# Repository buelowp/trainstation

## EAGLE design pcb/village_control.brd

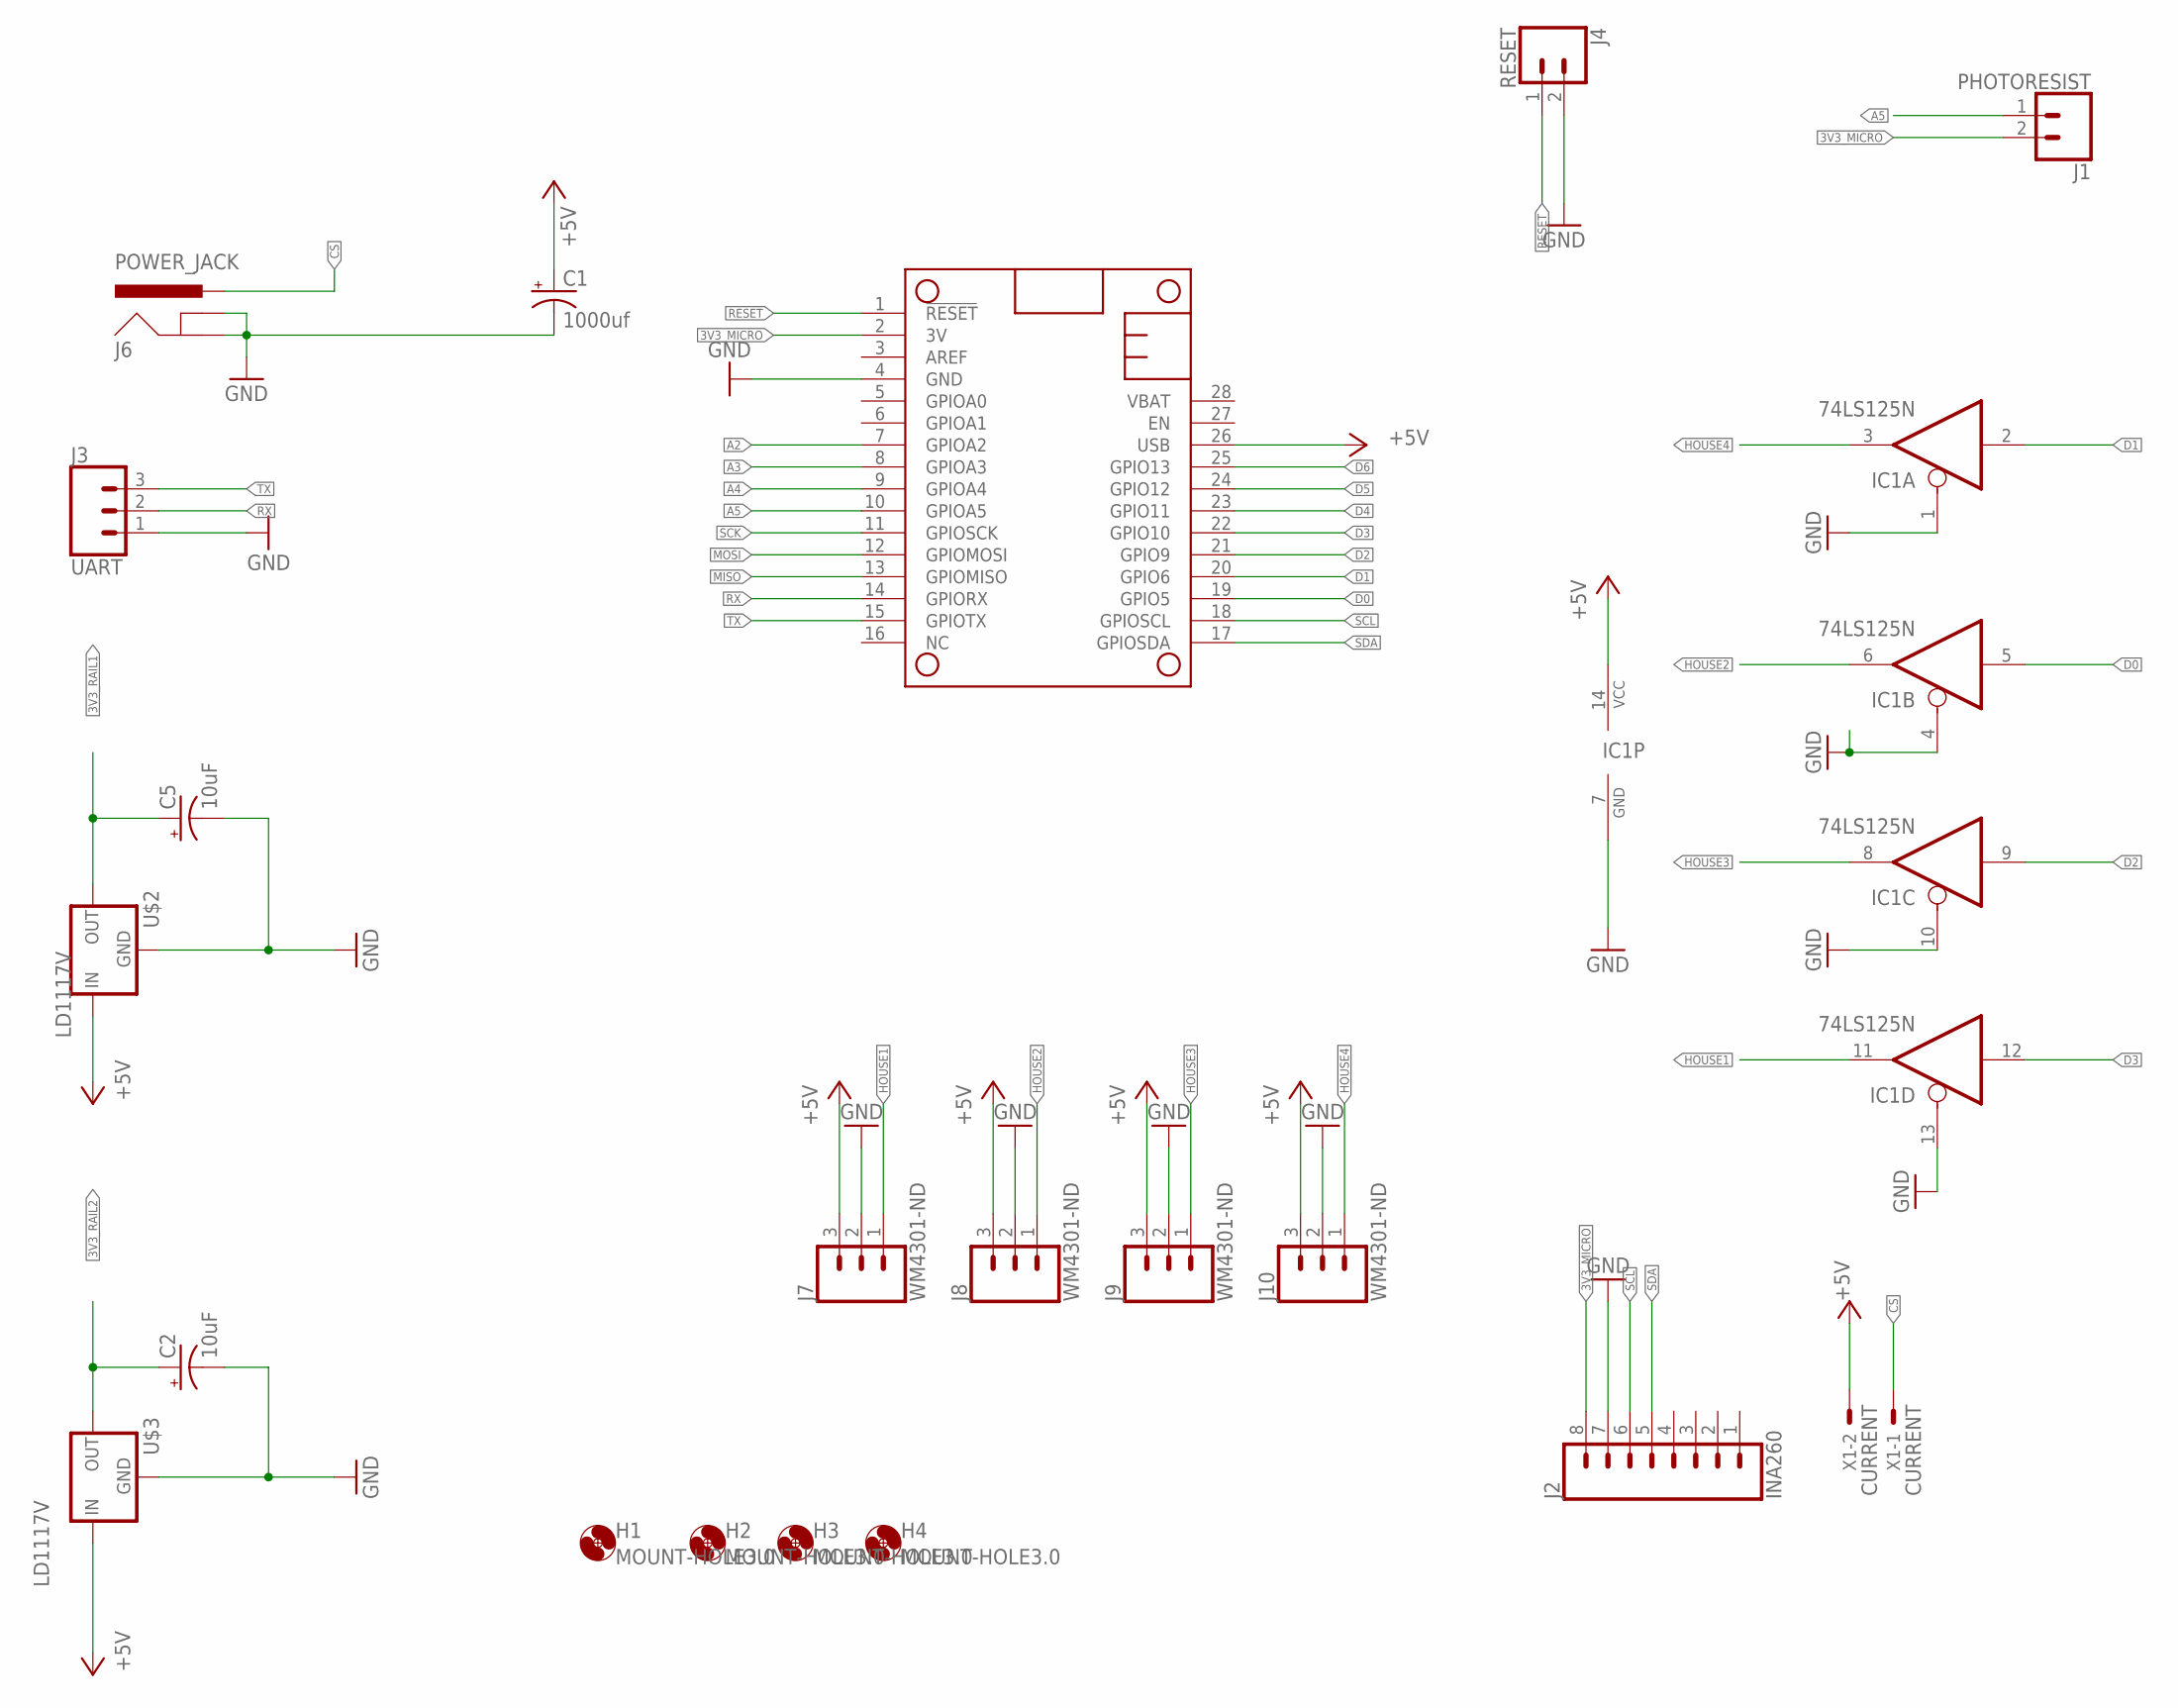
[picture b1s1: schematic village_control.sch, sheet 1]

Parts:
C1: 1000uf; CPOL-RADIAL-5MM-10MM
C2, C5: 10uF; CPOL-RADIAL-2.5MM-5MM-KIT
H1, H2, H3, H4: MOUNT-HOLE3.0; 3,0
IC1: 74LS125N; DIL14
J1: PHOTORESIST; 1X02
J2: INA260; 1X08
J3: UART; 1X03
J4: RESET; 1X02
J6: POWER_JACK; POWER_JACK_PTH
J7, J8, J9, J10: WM4301-ND; 1X03
MS2: FEATHERWING_NODIM; FEATHERWING_DIM
U$2, U$3: LD1117V; 78XXL
X1: CURRENT; KK-156-2

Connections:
3V3_MICRO: J1.2, J2.8, MS2.2 (3V)
3V3_RAIL1: C5.1 (+), U$2.GND (OUT); also elsewhere on the board
3V3_RAIL2: C2.1 (+), U$3.GND (OUT); also elsewhere on the board
+5V: C1.+, IC1.14 (VCC), J7.3, J8.3, J9.3, J10.3, MS2.26 (USB), U$2.OUT (IN), U$3.OUT (IN), X1.2; also elsewhere on the board
A2: MS2.7 (GPIOA2); also elsewhere on the board
A3: MS2.8 (GPIOA3); also elsewhere on the board
A4: MS2.9 (GPIOA4); also elsewhere on the board
A5: J1.1, MS2.10 (GPIOA5)
CS: J6.PWR, X1.1
D0: IC1.5 (I), MS2.19 (GPIO5)
D1: IC1.2 (I), MS2.20 (GPIO6)
D2: IC1.9 (I), MS2.21 (GPIO9)
D3: IC1.12 (I), MS2.22 (GPIO10)
D4: MS2.23 (GPIO11); also elsewhere on the board
D5: MS2.24 (GPIO12); also elsewhere on the board
D6: MS2.25 (GPIO13); also elsewhere on the board
GND: C1.-, C2.2 (-), C5.2 (-), IC1.1 (OE), IC1.4 (OE), IC1.7 (GND), IC1.10 (OE), IC1.13 (OE), J2.7, J3.1, J4.2, J6.GND, J6.GNDBREAK, J7.2, J8.2, J9.2, J10.2, MS2.4 (GND), U$2.IN (GND), U$3.IN (GND); also elsewhere on the board
HOUSE1: IC1.11 (O), J7.1
HOUSE2: IC1.6 (O), J8.1
HOUSE3: IC1.8 (O), J9.1
HOUSE4: IC1.3 (O), J10.1
MISO: MS2.13 (GPIOMISO); also elsewhere on the board
MOSI: MS2.12 (GPIOMOSI); also elsewhere on the board
RESET: J4.1, MS2.1 (!RESET)
RX: J3.2, MS2.14 (GPIORX)
SCK: MS2.11 (GPIOSCK); also elsewhere on the board
SCL: J2.6, MS2.18 (GPIOSCL)
SDA: J2.5, MS2.17 (GPIOSDA)
TX: J3.3, MS2.15 (GPIOTX)

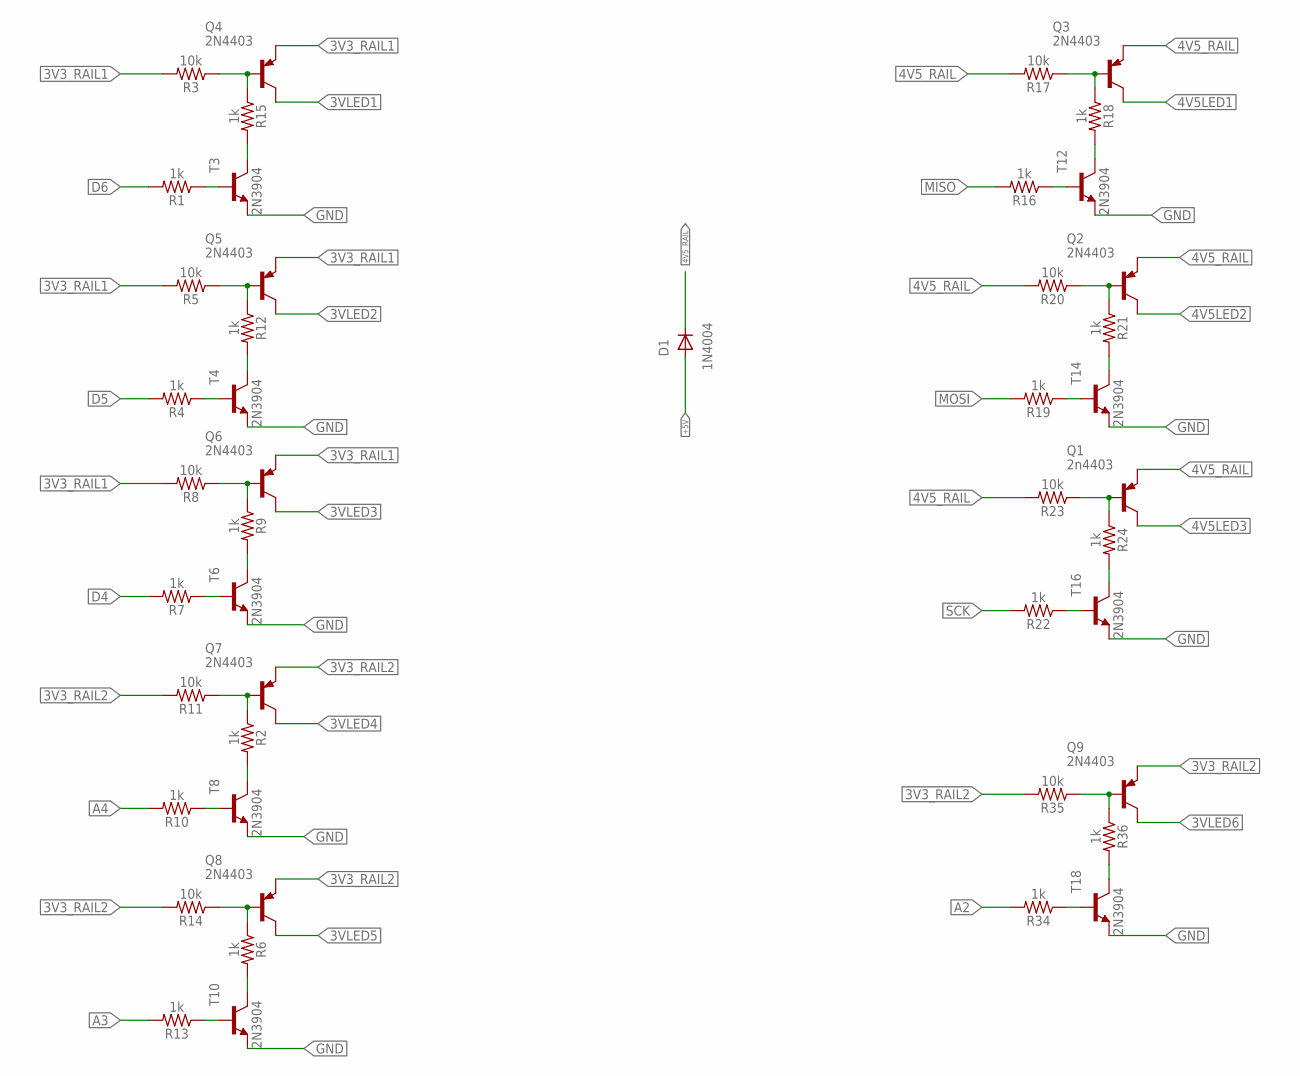
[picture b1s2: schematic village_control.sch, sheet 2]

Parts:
D1: 1N4004; DO41-10
Q1: 2n4403; TO92
Q2, Q3, Q4, Q5, Q6, Q7, Q8, Q9: 2N4403; TO92
R1, R2, R4, R6, R7, R9, R10, R12, R13, R15, R16, R18, R19, R21, R22, R24, R34, R36: 1k; AXIAL-0.3
R3, R5, R8, R11, R14, R17, R20, R23, R35: 10k; AXIAL-0.3
T3, T4, T6, T8, T10, T12, T14, T16, T18: 2N3904; TO92

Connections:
3V3_RAIL1: Q4.3 (E), Q5.3 (E), Q6.3 (E), R3.P$2 (2), R5.P$2 (2), R8.P$2 (2); also elsewhere on the board
3V3_RAIL2: Q7.3 (E), Q8.3 (E), Q9.3 (E), R11.P$2 (2), R14.P$2 (2), R35.P$2 (2); also elsewhere on the board
3VLED1: Q4.1 (C); also elsewhere on the board
3VLED2: Q5.1 (C); also elsewhere on the board
3VLED3: Q6.1 (C); also elsewhere on the board
3VLED4: Q7.1 (C); also elsewhere on the board
3VLED5: Q8.1 (C); also elsewhere on the board
3VLED6: Q9.1 (C); also elsewhere on the board
4V5LED1: Q3.1 (C); also elsewhere on the board
4V5LED2: Q2.1 (C); also elsewhere on the board
4V5LED3: Q1.1 (C); also elsewhere on the board
4V5_RAIL: D1.C, Q1.3 (E), Q2.3 (E), Q3.3 (E), R17.P$2 (2), R20.P$2 (2), R23.P$2 (2)
+5V: D1.A; also elsewhere on the board
A2: R34.P$2 (2); also elsewhere on the board
A3: R13.P$2 (2); also elsewhere on the board
A4: R10.P$2 (2); also elsewhere on the board
D4: R7.P$2 (2); also elsewhere on the board
D5: R4.P$2 (2); also elsewhere on the board
D6: R1.P$2 (2); also elsewhere on the board
GND: T3.3 (E), T4.3 (E), T6.3 (E), T8.3 (E), T10.3 (E), T12.3 (E), T14.3 (E), T16.3 (E), T18.3 (E); also elsewhere on the board
MISO: R16.P$2 (2); also elsewhere on the board
MOSI: R19.P$2 (2); also elsewhere on the board
unnamed: Q4.2 (B), R3.P$1 (1), R15.P$1 (1)
unnamed: R9.P$2 (2), T6.1 (C)
unnamed: R4.P$1 (1), T4.2 (B)
unnamed: R2.P$2 (2), T8.1 (C)
unnamed: R7.P$1 (1), T6.2 (B)
unnamed: R6.P$2 (2), T10.1 (C)
unnamed: Q6.2 (B), R8.P$1 (1), R9.P$1 (1)
unnamed: R12.P$2 (2), T4.1 (C)
unnamed: R10.P$1 (1), T8.2 (B)
unnamed: R1.P$1 (1), T3.2 (B)
unnamed: Q7.2 (B), R2.P$1 (1), R11.P$1 (1)
unnamed: R15.P$2 (2), T3.1 (C)
unnamed: R13.P$1 (1), T10.2 (B)
unnamed: Q8.2 (B), R6.P$1 (1), R14.P$1 (1)
unnamed: R36.P$2 (2), T18.1 (C)
unnamed: R16.P$1 (1), T12.2 (B)
unnamed: Q5.2 (B), R5.P$1 (1), R12.P$1 (1)
unnamed: Q3.2 (B), R17.P$1 (1), R18.P$1 (1)
unnamed: R24.P$2 (2), T16.1 (C)
unnamed: R19.P$1 (1), T14.2 (B)
unnamed: Q2.2 (B), R20.P$1 (1), R21.P$1 (1)
unnamed: R21.P$2 (2), T14.1 (C)
unnamed: R22.P$1 (1), T16.2 (B)
unnamed: Q1.2 (B), R23.P$1 (1), R24.P$1 (1)
unnamed: R18.P$2 (2), T12.1 (C)
unnamed: R34.P$1 (1), T18.2 (B)
unnamed: Q9.2 (B), R35.P$1 (1), R36.P$1 (1)
SCK: R22.P$2 (2); also elsewhere on the board

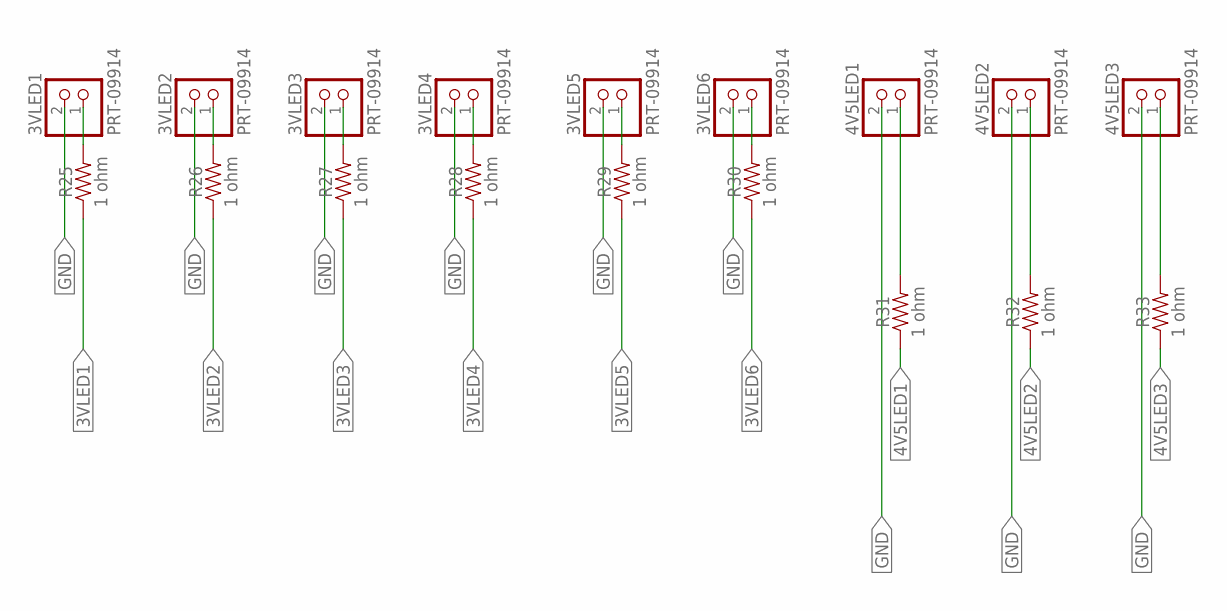
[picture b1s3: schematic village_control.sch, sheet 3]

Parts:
3VLED1, 3VLED2, 3VLED3, 3VLED4, 3VLED5, 3VLED6, 4V5LED1, 4V5LED2, 4V5LED3: PRT-09914; JST-PH-2-THM
R25, R26, R27, R28, R29, R30, R31, R32, R33: 1 ohm; AXIAL-0.3

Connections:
3VLED1: R25.P$1 (1); also elsewhere on the board
3VLED2: R26.P$1 (1); also elsewhere on the board
3VLED3: R27.P$1 (1); also elsewhere on the board
3VLED4: R28.P$1 (1); also elsewhere on the board
3VLED5: R29.P$1 (1); also elsewhere on the board
3VLED6: R30.P$1 (1); also elsewhere on the board
4V5LED1: R31.P$1 (1); also elsewhere on the board
4V5LED2: R32.P$1 (1); also elsewhere on the board
4V5LED3: R33.P$1 (1); also elsewhere on the board
GND: 3VLED1.2 (1), 3VLED2.2 (1), 3VLED3.2 (1), 3VLED4.2 (1), 3VLED5.2 (1), 3VLED6.2 (1), 4V5LED1.2 (1), 4V5LED2.2 (1), 4V5LED3.2 (1); also elsewhere on the board
unnamed: 3VLED1.1 (2), R25.P$2 (2)
unnamed: 4V5LED1.1 (2), R31.P$2 (2)
unnamed: 3VLED2.1 (2), R26.P$2 (2)
unnamed: 4V5LED2.1 (2), R32.P$2 (2)
unnamed: 3VLED3.1 (2), R27.P$2 (2)
unnamed: 4V5LED3.1 (2), R33.P$2 (2)
unnamed: 3VLED4.1 (2), R28.P$2 (2)
unnamed: 3VLED5.1 (2), R29.P$2 (2)
unnamed: 3VLED6.1 (2), R30.P$2 (2)

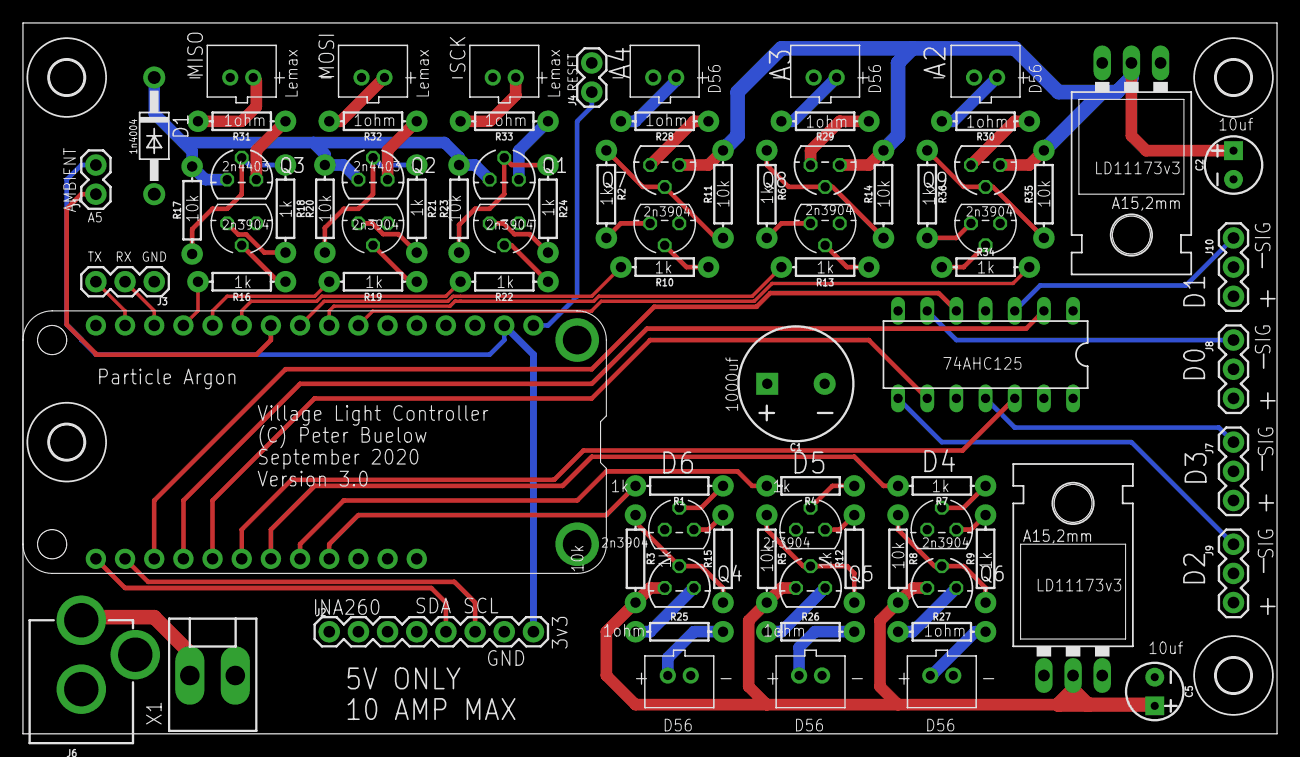
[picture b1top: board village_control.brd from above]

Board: 4 copper layers, 109.2 x 61.9 mm, 85 parts (0 on the bottom side), 75 nets.

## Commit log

2020-04-17 blink was running full bore, it never switched.
2020-09-03 Updating to Particle build system
2020-09-06 Continue to develop
    * Added some lights on and off logic, needs testing
2020-09-07 Checkpoint
    * Fixed it so the lights do what we need them to
    * Seperated the FastLED and Adafruit connections into classes to make it easier to manage the different parts
    * Added new gitignore
2020-09-07 Checkpoint
    * Added a block class to handle a collection of houses
    * Fixed up houses with logging and a few logical changes
    * Modified loop() to turn houses on and off randomly I believe, still testing
2020-09-08 New functionality
    * Added the ability to control the individual LED pins, which are street lamps mostly
    * Fixed a lot of bugs with the houses, and blocks of houses logic
    * Fixed a lot of logic related to turning on and off houses around sunrise and sunset
2020-09-08 Adding the controller PCB to the stored contents
2020-09-09 Fixing a bug
    * I switched the parameters for hasBeenTested() in turnOffRandomHouse() which caused some issues
    * Made the 1 minute HB print one hour just cause
2020-09-16 Lots of fixes.
    * Fixed bugs related to when lights turn on and off
    * Cleaned up logic issues
    * Made sure timeset only runs once
2020-09-18 Many fixes
    * Fixed an issue where the station didn't start correctly, so it wouldn't turn off
    * Fixed some indexing issues for the FastLED CRGB arrays
    * Many printing changes
    * Work towards fixing the number of lights that turn on/off in the random, still seems to have an issue
2020-10-10 Various fixes
2020-10-13 Migrating to new house branch
    * Create a class structure to support both FastLED and Adafruit LEDs
2020-11-14 Updates
    * Fixed some issues related to turning signals on and off
    * Migrating to all Adafruit code for lighting
2020-11-15 Lots of fixes
    * Provide the houses base with a turnon + brightness
    * Fixed a bug in the ada houses which made sure they wouldn't turn on
    * Fix turning houses off if lights are still no after 10
2020-11-16 Fixes issues and gets it working
    * Changed how I determine which houses can be turned on for random
    * Fixed bugs in the houses
    * Added MQTT messaging to make it easier to see what's happening
2020-11-18 Fixing some issues
    * Add village.* to git, it was missing before
    * Fix issues turning lights on/off correctly
    * Added some new methods for house control
    * Fixed issues with RGBW support for houses
2020-11-24 Issue #2: Adding color to the houses

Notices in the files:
parts and their libraries:
SparkFun-Capacitors: Licensing: Creative Commons ShareAlike 4.0 International - https://creativecommons.org/licenses/by-sa/4.0
